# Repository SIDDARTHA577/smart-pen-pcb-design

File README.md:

# Smart Pen Hardware & Mechanical Engineering Project

A compact, pen-sized embedded electronic hardware platform and mechanical assembly designed for handwriting motion capture, local sensor data logging, and digital stroke reconstruction.

---

## 1. Project Overview

The **Smart Pen** is an integrated embedded systems project that combines motion sensing, local storage, capacitive touch handwriting detection, and wireless communication into a slender pen-form-factor mechanical enclosure.

### Core Architecture & Operating Concept
- **Handwriting Detection**: Ergonomic capacitive touch sensor on the pen grip detects when the user's finger touches the pen during active writing (`WRITE/RECORD` event).
- **Motion Tracking**: 6-DOF Inertial Measurement Unit (IMU) positioned in the forward pen tip pocket near the refill nib captures continuous acceleration and angular velocity.
- **Local Logging**: High-speed MicroSD storage records raw IMU streams and touch event telemetry.
- **Connectivity & Processing**: Espressif ESP32-C3 RISC-V microcontroller with 2.4 GHz Wi-Fi 4, Bluetooth 5 (LE), and native USB CDC-ACM communication.
- **Mechanical Form Factor**: Removable internal electronics rail/cartridge fitted with a bayonet lock collar, allowing the pen to be serviced as a single unit while accommodating a standard D1 ballpoint ink refill and rear mechanical click ratchet mechanism.

---

## 2. Distributed Electronic Hardware Architecture

To achieve a maximum outer barrel diameter $\le 16.0\text{ mm}$ while accommodating a central ink refill cartridge and mechanical click spring, the electronics are partitioned across a **4-board distributed topology**:

```
                              ┌────────────────────────────────────────┐
                              │           Main PCB (SmartPen)          │
                              │      84.00 x 9.20 mm, 2-layer FR4      │
                              │   ESP32-C3FH4, MCP73831, AP2112K-3.3   │
                              └───────┬────────────┬────────────┬──────┘
                                      │            │            │
                         JST-SH 4-pin │            │            │ 6-pin FPC
                                      │            │            │
                                      ▼            │            ▼
                     ┌──────────────────────┐      │   ┌──────────────────────┐
                     │ Front MPU Board      │      │   │ MicroSD Carrier      │
                     │ 8.00 x 10.00 mm      │      │   │ 11.00 x 12.00 mm     │
                     │ InvenSense MPU-6050  │      │   │ Hirose DM3D-SF Slot  │
                     └──────────────────────┘      │   └──────────────────────┘
                                                   │
                                      JST-SH 3-pin │
                                                   ▼
                                      ┌──────────────────────┐
                                      │ Touch Sensor Board   │
                                      │ 6.00 x 18.00 mm      │
                                      │ TonTek TTP223-BA6    │
                                      └──────────────────────┘
```

### Board Specifications & Bill of Materials

| Board Module | Dimensions | Key Active ICs / Connectors | Interface to Main | Fabrication DRC Status |
| :--- | :--- | :--- | :--- | :--- |
| **Main PCB** (`SmartPen`) | $84.00 \times 9.20 \times 1.00\text{ mm}$ | Espressif ESP32-C3FH4 (4MB Flash), Microchip MCP73831T-2ACI/OT ($303\text{ mA}$ charger), Diodes Inc DMG2305UX P-FET (Power-Path), Diodes Inc AP2112K-3.3 ($600\text{ mA}$ LDO), Microchip MCP23008T-E/ML ($I^2C$ Expander), 1027 Coin Haptic Motor, USB-C 16-pin (`J1`), SPDT Slide Switch (`SW3`) | N/A (Master Host) | **ERC PASS** (0 Errors, 0 Warnings)<br>Layout: 704 clearance DRCs (Engineering Draft) |
| **Touch Sensor** (`Touch_Sensor`) | $6.00 \times 18.00 \times 0.80\text{ mm}$ | TonTek TTP223-BA6 SOT-23-6 touch controller, $5.0 \times 10.0\text{ mm}$ copper touch electrode (`E1`) | JST-SH 3-pin ($1.0\text{ mm}$) | **100% CLEAN DRC** (0 violations, 0 unrouted nets) |
| **Front MPU** (`Front_MPU`) | $8.00 \times 10.00 \times 0.80\text{ mm}$ | InvenSense MPU-6050 QFN-24 6-axis gyro/accel | JST-SH 4-pin ($1.0\text{ mm}$) | **ERC PASS** (0 Errors)<br>Layout: 25 clearance DRCs |
| **MicroSD Carrier** (`MicroSD_Carrier`) | $11.00 \times 12.00 \times 0.80\text{ mm}$ | Hirose DM3D-SF push-push MicroSD receptacle | 6-pin FPC ($0.5\text{ mm}$) | **ERC PASS** (0 Errors)<br>Layout: 214 clearance DRCs |

### Power Management Subsystem
- **Battery Compatibility**: Single-cell LiPo / Li-ion (e.g., LP401040, 130–150 mAh, nominal 3.7 V).
- **Charging Circuit**: Microchip MCP73831T linear charge management controller programmed to $I_{CHG} = 303\text{ mA}$ via a $3.3\text{ k}\Omega$ resistor on `PROG`.
- **Dynamic Power-Path**: Low-$R_{DS(on)}$ P-channel MOSFET (DMG2305UX, $52\text{ m}\Omega$) + Schottky barrier diode (MBR0520L, $V_F \approx 0.34\text{ V}$). Seamlessly powers the system from USB VBUS ($5.0\text{ V}$) when connected, preventing unnecessary battery charge/discharge cycles.
- **System Voltage Rail**: AP2112K-3.3 LDO regulator providing up to $600\text{ mA}$ continuous output at $3.3\text{ V}$ with $250\text{ mV}$ dropout at full load to satisfy ESP32-C3 RF transmission burst current demands.

---

## 3. Mechanical & 3D Enclosure Design

The mechanical design is parametrically generated using OpenCASCADE / CadQuery scripts (`scripts/build_cad_enclosure.py`).

### Key Enclosure Specifications
- **Maximum Outer Diameter**: $15.50\text{ mm}$ (within $\le 16.0\text{ mm}$ ergonomic constraint).
- **Total Assembly Length**: $\approx 155.0\text{ mm}$ (standard pen length).
- **Ink Refill Standard**: Standard D1 refill cartridge ($67.0\text{ mm} \times \varnothing 2.3\text{ mm}$) with front return spring and rear ratchet mechanism.
- **Removable Internal Rail**: Houses the battery cradle below the main PCB and includes a bayonet twist-lock collar ($30^\circ$ twist release) for rapid internal servicing.

### Deliverable CAD Files
- **Master STEP Assembly**: `SmartPen_Complete_Assembly.step` (742 KB)
- **14 Watertight 3D Printable STL Files** (`output/RevF_Client_Delivery/08_3D_STL/`):
  1. `01_Outer_Barrel.stl` — Main pen body casing
  2. `02_Front_Grip.stl` — Ergonomic grip with capacitive touch pad recess
  3. `03_Front_Cap_Tip.stl` — Tapered tip housing the refill nib
  4. `04_Internal_Rail_Cartridge.stl` — Serviceable electronics mounting spine
  5. `05_Battery_Cradle.stl` — Lower battery retention bay
  6. `06_Front_IMU_Carrier.stl` — Forward sensor mounting pocket
  7. `07_Dual_Button_Actuator.stl` — Push-button cap for Erase and Mode switches
  8. `08_Rear_Click_Mechanism_Cap.stl` — Retractable click plunger cap
  9. `09_Pocket_Clip.stl` — Integrated enclosure pocket clip
  10. `10_Vibration_Motor_Mount.stl` — 1027 haptic coin motor bracket
  11. `11_LiPo_Battery_LP401040.stl` — Battery volume mockup
  12. `12_D1_Ink_Refill_and_Spring.stl` — D1 refill clearance envelope
  13. `13_Click_Ratchet_and_Pushrod.stl` — Click mechanism mechanical linkage
  14. `14_Bayonet_Locking_Collar.stl` — Twist-lock retaining collar

---

## 4. Repository Directory Structure

```
.
├── .gitignore                                # Excludes pycache, local lockfiles, temp data
├── README.md                                 # Project documentation and engineering status
├── CubeTest.step                             # CAD mechanical test fixture
├── test_step.step                            # CAD mechanical test fixture
├── SmartPen-drc.rpt / erc.rpt                # Root KiCad DRC and ERC verification logs
│
├── KiCad/                                    # KiCad configuration and library directory
│   └── 10.0/                                 # KiCad 10.0 symbol and footprint environment
│
├── SmartPen_RevD_AutoLinked_DRAFT/           # Historical Revision D baseline
│   ├── 3D_Concept/                           # Early conceptual 3D models (STL & STEP)
│   ├── Docs/                                 # Footprint assignment audits and netlists
│   └── EasyEDA/                              # Legacy EasyEDA JSON project files
│
├── output/                                   # Build artifacts and release packages
│   ├── kicad/                                # Core intermediate KiCad project files
│   ├── RevE_work/                            # Revision E milestone files and Gerbers
│   ├── RevF_Working/                         # Active working directory for Revision F
│   │   ├── SmartPen.kicad_sch / .pcb         # Main PCB schematics and layout
│   │   ├── Touch_Sensor/                     # Touch sensor KiCad project
│   │   ├── Front_MPU/                        # Front IMU daughterboard KiCad project
│   │   ├── MicroSD_Carrier/                  # MicroSD daughterboard KiCad project
│   │   └── SmartPen.pretty/                  # Custom footprint library
│   ├── client_delivery/                      # Revision E complete zip package
│   └── RevF_Client_Delivery/                 # Revision F formal delivery package
│       ├── 01_EasyEDA_Source/                # EasyEDA Pro JSON exports
│       ├── 02_KiCad_Source/                  # KiCad schematics, layouts, libraries
│       ├── 03_PDF_Schematic/                 # High-resolution vector schematic PDFs
│       ├── 04_Gerber_Drill/                  # RS-274X Gerbers and Excellon drill files
│       ├── 05_BOM_CPL/                       # Full BOMs and pick-and-place centroids
│       ├── 06_Fabrication_Drawing/           # Board fabrication mechanical specs
│       ├── 07_3D_CAD_Source/                 # Python parametric CAD source scripts
│       ├── 07_3D_STEP/                       # STEP assembly and component models
│       ├── 08_3D_STL/                        # 14 watertight STL models for 3D printing
│       ├── 09_Mechanical_Drawings/           # Dimensioned mechanical PDFs
│       ├── 10_Assembly_Guide/                # Step-by-step mechanical assembly manual
│       ├── 11_Reports/                       # DRC, ERC, and engineering audit logs
│       ├── 12_Verification_Suite/            # Python automated verification test suite
│       └── SmartPen_RevF_Digital_Design_Review_Package.zip
│
├── reports/                                  # Engineering audit and sign-off reports
│   ├── baseline_audit.md                     # Initial design audit and gap analysis
│   ├── FINAL_VALIDATION.md                   # Digital design gate validation report
│   ├── MECHANICAL_VALIDATION.md              # Collision and motion sweep analysis
│   ├── TEST_MATRIX.csv                       # Requirements verification matrix
│   └── RevF/                                 # Detailed Rev F technical review reports
│       ├── BASELINE_AUDIT.md
│       ├── FINAL_ENGINEERING_REPORT.md       # Master engineering sign-off report
│       ├── POWER_AND_BATTERY_REVIEW.md
│       ├── POWER_PATH_DESIGN.md
│       ├── TOUCH_AND_GPIO_ARCHITECTURE.md
│       ├── USB_ARCHITECTURE_AND_TETHERING.md
│       └── VERIFICATION_AUDIT_LOG.md
│
├── scripts/                                  # CAD generation and PCB routing engine
│   ├── build_cad_enclosure.py                # Parametric 3D CAD generator
│   ├── highway_astar_router.py               # Custom A* PCB maze router
│   ├── solve_clean_geometry.py               # Algorithmic component placement optimizer
│   └── ... (230 Python automation scripts)
│
└── tests/                                    # Automated pytest regression suite
    ├── test_assembly_cad.py                  # STEP/STL watertightness and bounding tests
    ├── test_assembly_clearance.py            # Component collision verification
    ├── test_delivery_integrity.py            # Delivery file presence and checksums
    ├── test_front_mpu.py                     # MPU board netlist and footprint checks
    ├── test_gerbers.py                       # Gerber layer completeness
    ├── test_gpio_architecture.py             # GPIO assignment verification
    ├── test_mechanical.py                    # Mechanical enclosure dimensions
    ├── test_microsd_carrier.py               # MicroSD carrier pinout validation
    ├── test_netlist.py                       # Netlist integrity tests
    ├── test_pcb.py                           # Board outline and layer tests
    ├── test_power_path.py                    # Power-path circuit connectivity
    ├── test_schematic.py                     # KiCad ERC report validation
    └── test_touch_sensor.py                  # Touch daughterboard DRC tests
```

---

## 5. Development Status & Engineering Gates

### Formal Verification Gate Breakdown

```
[ DIGITAL DESIGN GATE ] ─────────► PASS (94.8% Weighted Completion)
  ├─ 4 Schematic ERC checks ─────► 0 Errors, 0 Warnings (100% PASS)
  ├─ Touch Sensor PCB DRC ───────► 0 Violations (100% Clean)
  ├─ 3D CAD Watertightness ──────► 14/14 STL Models 2-Manifold Validated
  └─ Automated Test Suite ───────► 46/46 Unit Tests PASS (100%)

[ FABRICATION RELEASE GATE ] ────► GATED (Engineering Draft)
  ├─ Main PCB High-Density Routing ► 704 clearance DRC flags (Requires interactive polish)
  ├─ MicroSD Carrier Routing ────► 214 clearance DRC flags
  ├─ Front MPU Routing ──────────► 25 clearance DRC flags
  └─ Physical Prototyping ───────► Awaiting physical fit check & thermal test
```

### Clearly Distinguished Status Categories

#### Completed & Mathematically Verified
- Schematic ERC: All 4 schematics compile with **0 Errors, 0 Warnings** under official `kicad-cli sch erc`.
- Touch Sensor PCB: Achieved **0 DRC violations** under `kicad-cli pcb drc`.
- Power Architecture: Charging current ($303\text{ mA}$), dynamic power-path P-FET steering, and $600\text{ mA}$ LDO regulation verified by simulation and netlist audits.
- Automated Test Suite: All **46 unit tests** in `tests/` pass under pytest.
- 3D CAD Models: All 14 STL solid bodies confirmed watertight (2-manifold) with zero non-manifold edges.

#### Known Issues & Engineering Draft Items
- **High-Density Auto-Routed Clearance Flags**:
  - The algorithmic router generated working topological paths on 2 layers, but due to the dense $0.4\text{ mm}$ and $0.5\text{ mm}$ pitch pads on the ESP32-C3 QFN-32 and MCP23008 QFN-20 packages, clearance DRC violations exist (704 on Main PCB, 214 on MicroSD Carrier, 25 on Front MPU).
  - *Recommendation*: Interactive manual routing polish in KiCad with micro-vias or neck-down traces before ordering physical fabrication.
- **ESP32-C3 USB Host Limitation**:
  - The ESP32-C3 hardware USB peripheral is a USB-Serial/JTAG CDC device controller. It does not contain USB Host silicon.
  - Wired phone tethering via USB Host is physically unsupported on this chip. Mobile internet backhaul must be handled over **Wi-Fi SoftAP / Personal Hotspot or Bluetooth PAN**.

#### Planned Features (Post-Hardware Bringup)
- Firmware development for continuous IMU quaternion filter / sensor fusion.
- Browser-based handwriting stroke rendering engine.
- Machine learning handwriting character classification pipeline.

---

## 6. How to Open and Review the Project

### Prerequisites
- **PCB Design**: [KiCad 8.0 or 10.0](https://www.kicad.org/) (native projects located in `output/RevF_Working/` and `output/RevF_Client_Delivery/02_KiCad_Source/`).
- **Legacy EDA**: [EasyEDA Pro](https://pro.easyeda.com/) for JSON exports in `output/RevF_Client_Delivery/01_EasyEDA_Source/`.
- **3D CAD**: [FreeCAD](https://www.freecad.org/), Autodesk Fusion 360, or any STEP/STL viewer for files in `output/RevF_Client_Delivery/07_3D_STEP/`.
- **Python Environment**: Python 3.10+ with `pytest` for automated test execution.

### Running the Test Suite
To run the complete automated test suite:
```bash
python -m pytest tests/
```
Expected output: `46 passed in ~5s`.

### Opening in KiCad
1. Launch KiCad.
2. Select **File > Open Project**.
3. Navigate to `output/RevF_Working/SmartPen.kicad_pro` (or the daughterboards in `output/RevF_Working/Front_MPU/`, `MicroSD_Carrier/`, and `Touch_Sensor/`).
4. Inspect schematics in Eeschema and layouts in Pcbnew.

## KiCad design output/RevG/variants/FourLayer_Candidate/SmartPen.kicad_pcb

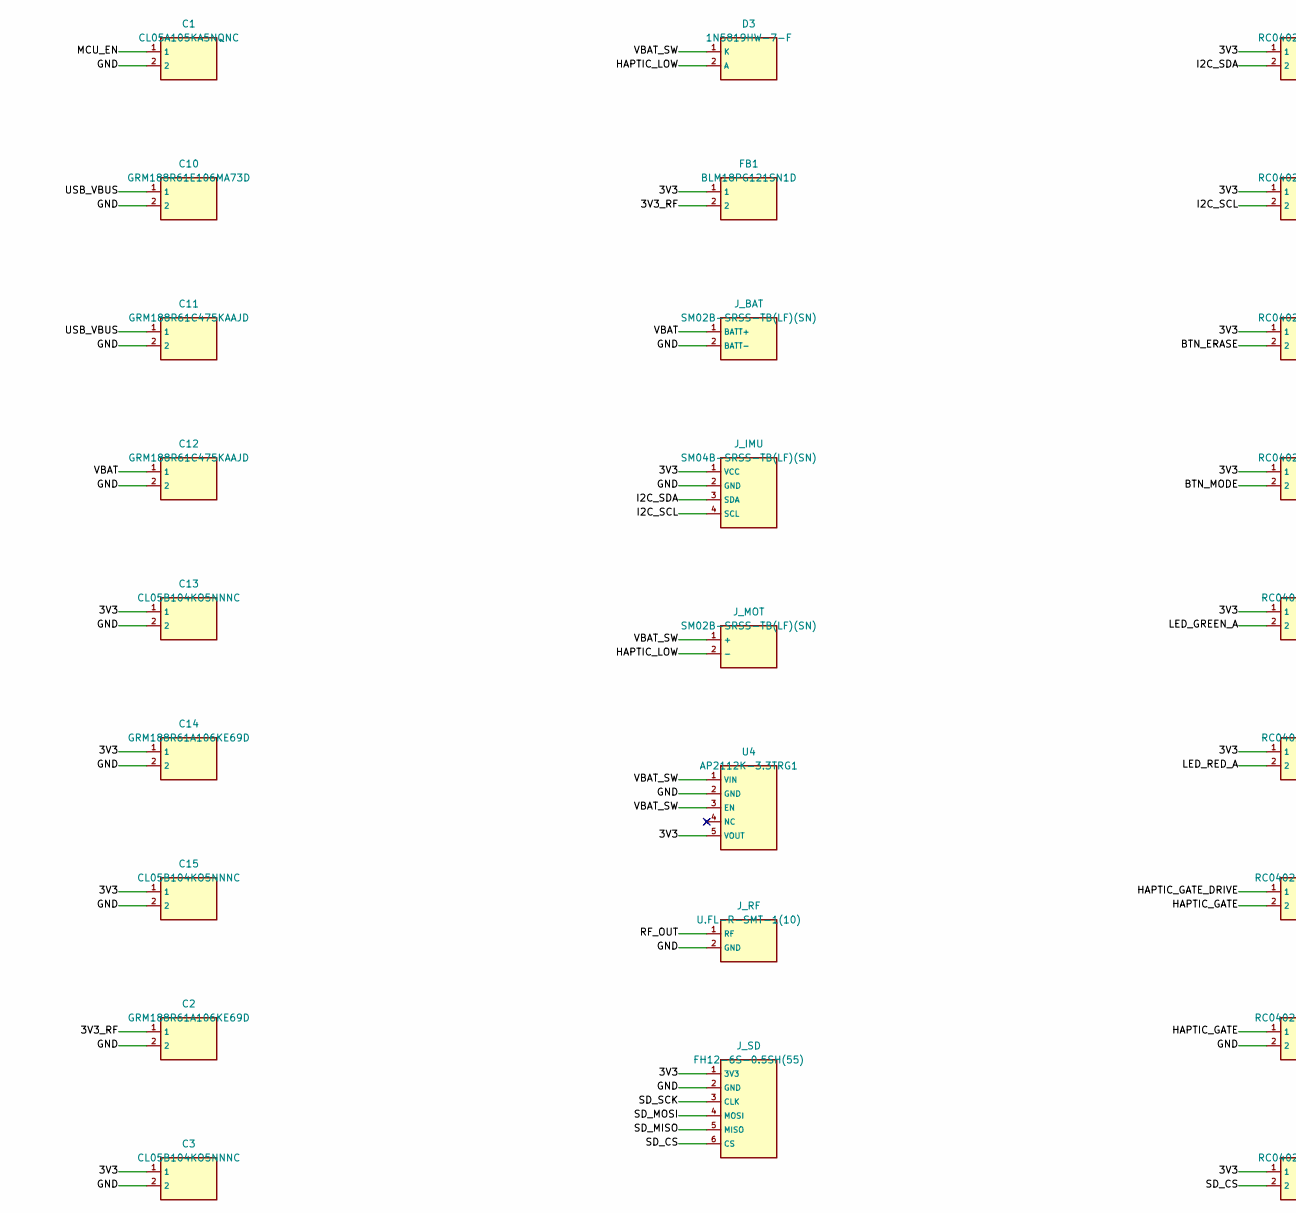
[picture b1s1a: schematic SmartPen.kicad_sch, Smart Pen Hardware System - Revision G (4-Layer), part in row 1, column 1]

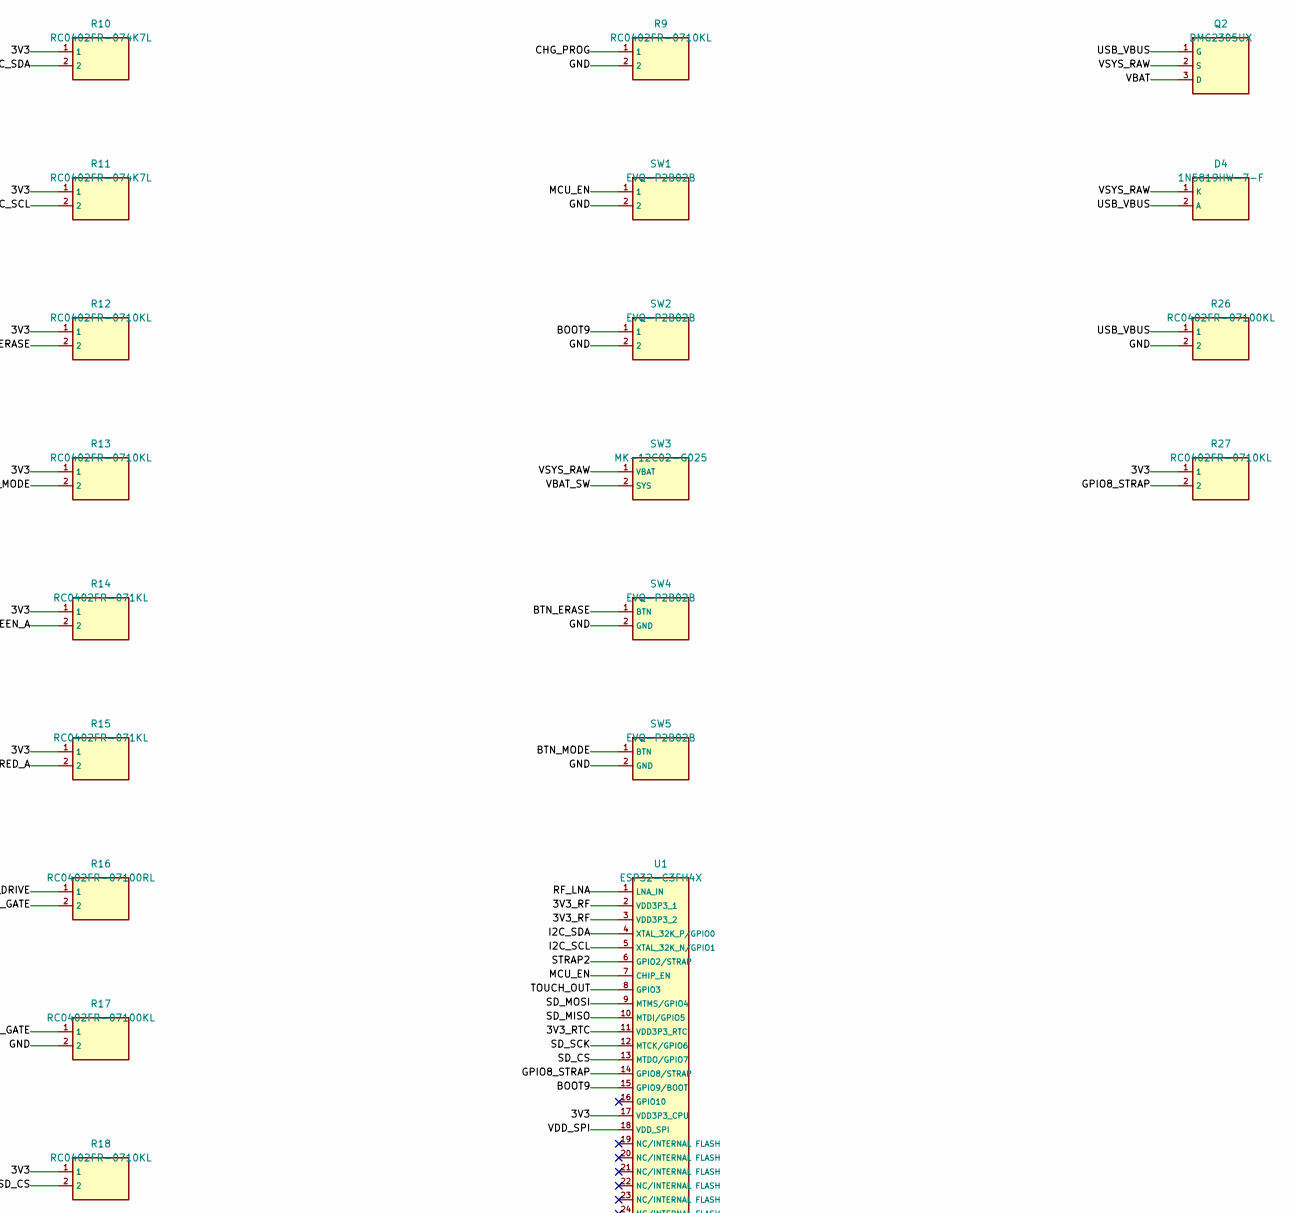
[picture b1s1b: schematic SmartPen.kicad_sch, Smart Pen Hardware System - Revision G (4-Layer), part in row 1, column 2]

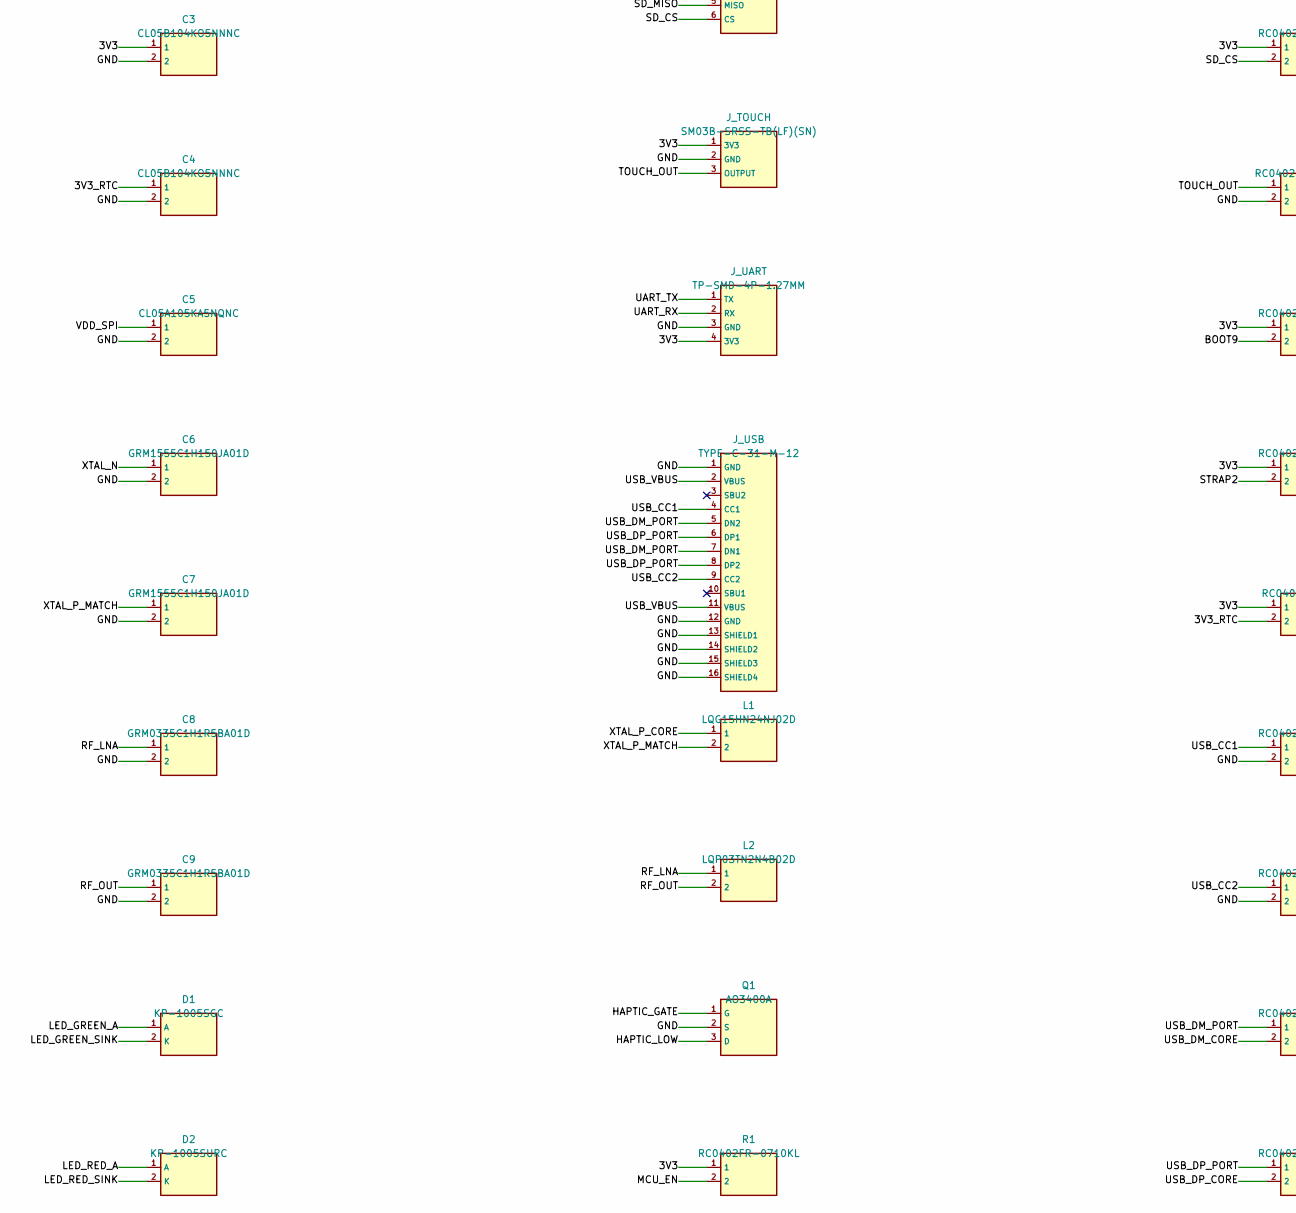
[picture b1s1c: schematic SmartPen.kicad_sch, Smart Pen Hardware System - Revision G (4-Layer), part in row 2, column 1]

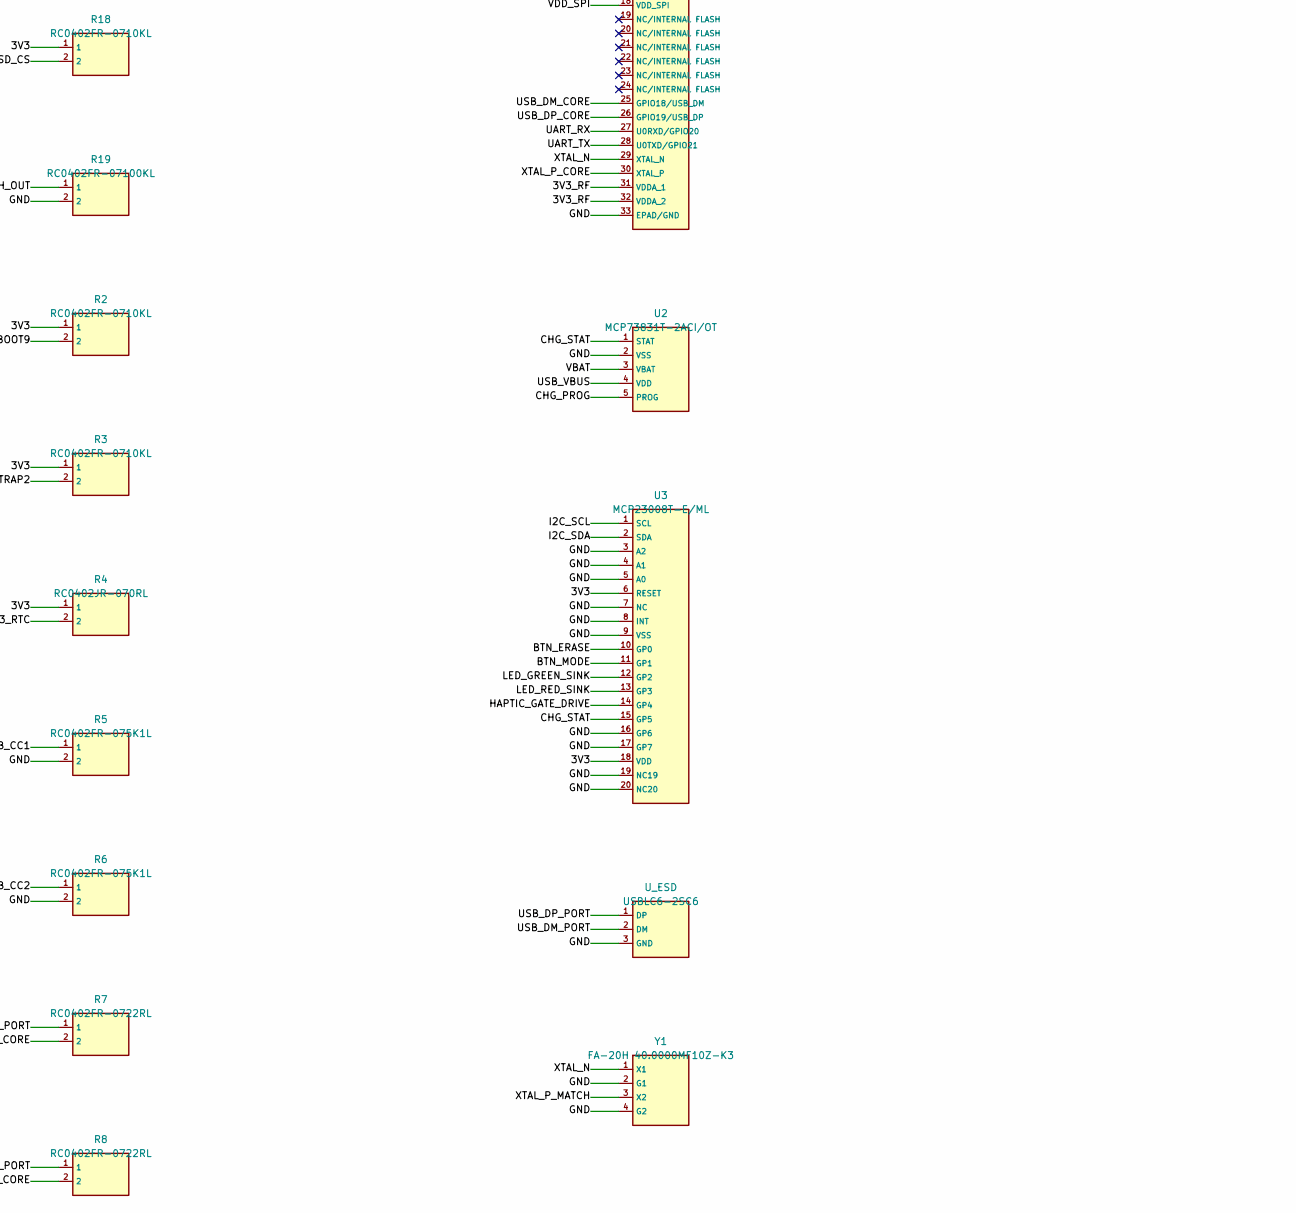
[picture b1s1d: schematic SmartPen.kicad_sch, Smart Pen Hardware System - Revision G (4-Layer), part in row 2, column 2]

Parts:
C1: CL05A105KA5NQNC; C1
C2: GRM188R61A106KE69D; C2
C3: CL05B104KO5NNNC; C3
C4: CL05B104KO5NNNC; C4
C5: CL05A105KA5NQNC; C5
C6: GRM1555C1H150JA01D; C6
C7: GRM1555C1H150JA01D; C7
C8: GRM0335C1H1R5BA01D; C8
C9: GRM0335C1H1R5BA01D; C9
C10: GRM188R61E106MA73D; C10
C11: GRM188R61C475KAAJD; C11
C12: GRM188R61C475KAAJD; C12
C13: CL05B104KO5NNNC; C13
C14: GRM188R61A106KE69D; C14
C15: CL05B104KO5NNNC; C15
D1: KP-1005SGC; D1
D2: KP-1005SURC; D2
D3: 1N5819HW-7-F; D3
D4: 1N5819HW-7-F; D4
FB1: BLM18PG121SN1D; FB1
J_BAT: SM02B-SRSS-TB(LF)(SN); J_BAT
J_IMU: SM04B-SRSS-TB(LF)(SN); J_IMU
J_MOT: SM02B-SRSS-TB(LF)(SN); J_MOT
J_RF: U.FL-R-SMT-1(10); J_RF
J_SD: FH12-6S-0.5SH(55); J_SD
J_TOUCH: SM03B-SRSS-TB(LF)(SN); J_TOUCH
J_UART: TP-SMD-4P-1.27MM; J_UART
J_USB: TYPE-C-31-M-12; J_USB
L1: LQG15HN24NJ02D; L1
L2: LQP03TN2N4B02D; L2
Q1: AO3400A; Q1
Q2: DMG2305UX; Q1
R1: RC0402FR-0710KL; R1
R2: RC0402FR-0710KL; R2
R3: RC0402FR-0710KL; R3
R4: RC0402JR-070RL; R4
R5: RC0402FR-075K1L; R5
R6: RC0402FR-075K1L; R6
R7: RC0402FR-0722RL; R7
R8: RC0402FR-0722RL; R8
R9: RC0402FR-0710KL; R9
R10: RC0402FR-074K7L; R10
R11: RC0402FR-074K7L; R11
R12: RC0402FR-0710KL; R12
R13: RC0402FR-0710KL; R13
R14: RC0402FR-071KL; R14
R15: RC0402FR-071KL; R15
R16: RC0402FR-07100RL; R16
R17: RC0402FR-07100KL; R17
R18: RC0402FR-0710KL; R18
R19: RC0402FR-07100KL; R19
R26: RC0402FR-07100KL; R1
R27: RC0402FR-0710KL; R27
SW1: EVQ-P2B02B; SW1
SW2: EVQ-P2B02B; SW2
SW3: MK-12C02-G025; SW3
SW4: EVQ-P2B02B; SW4
SW5: EVQ-P2B02B; SW5
U1: ESP32-C3FH4X; U1
U2: MCP73831T-2ACI/OT; U2
U3: MCP23008T-E/ML; U3
U4: AP2112K-3.3TRG1; J_PWR
U_ESD: USBLC6-2SC6; U_ESD
Y1: FA-20H 40.0000MF10Z-K3; Y1

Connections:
/3V3: C3.1, C13.1, C14.1, C15.1, FB1.1, J_IMU.1 (VCC), J_SD.1 (3V3), J_TOUCH.1 (3V3), J_UART.4 (3V3), R1.1, R2.1, R3.1, R4.1, R10.1, R11.1, R12.1, R13.1, R14.1, R15.1, R18.1, R27.1, U1.17 (VDD3P3_CPU), U3.6 (RESET), U3.18 (VDD), U4.5 (VOUT)
/3V3_RF: C2.1, FB1.2, U1.2 (VDD3P3_1), U1.3 (VDD3P3_2), U1.31 (VDDA_1), U1.32 (VDDA_2)
/3V3_RTC: C4.1, R4.2, U1.11 (VDD3P3_RTC)
/BOOT9: R2.2, SW2.1, U1.15 (GPIO9/BOOT)
/BTN_ERASE: R12.2, SW4.1 (BTN), U3.10 (GP0)
/BTN_MODE: R13.2, SW5.1 (BTN), U3.11 (GP1)
/CHG_PROG: R9.1, U2.5 (PROG)
/CHG_STAT: U2.1 (STAT), U3.15 (GP5)
/GND: C1.2, C2.2, C3.2, C4.2, C5.2, C6.2, C7.2, C8.2, C9.2, C10.2, C11.2, C12.2, C13.2, C14.2, C15.2, J_BAT.2 (BATT-), J_IMU.2 (GND), J_RF.2 (GND), J_SD.2 (GND), J_TOUCH.2 (GND), J_UART.3 (GND), J_USB.1 (GND), J_USB.12 (GND), J_USB.13 (SHIELD1), J_USB.14 (SHIELD2), J_USB.15 (SHIELD3), J_USB.16 (SHIELD4), Q1.2 (S), R5.2, R6.2, R9.2, R17.2, R19.2, R26.2, SW1.2, SW2.2, SW4.2 (GND), SW5.2 (GND), U1.33 (EPAD/GND), U2.2 (VSS), U3.3 (A2), U3.4 (A1), U3.5 (A0), U3.7 (NC), U3.8 (INT), U3.9 (VSS), U3.16 (GP6), U3.17 (GP7), U3.19 (NC19), U3.20 (NC20), U4.2 (GND), U_ESD.3 (GND), Y1.2 (G1), Y1.4 (G2)
/GPIO8_STRAP: R27.2, U1.14 (GPIO8/STRAP)
/HAPTIC_GATE: Q1.1 (G), R16.2, R17.1
/HAPTIC_GATE_DRIVE: R16.1, U3.14 (GP4)
/HAPTIC_LOW: D3.2 (A), J_MOT.2 (-), Q1.3 (D)
/I2C_SCL: J_IMU.4 (SCL), R11.2, U1.5 (XTAL_32K_N/GPIO1), U3.1 (SCL)
/I2C_SDA: J_IMU.3 (SDA), R10.2, U1.4 (XTAL_32K_P/GPIO0), U3.2 (SDA)
/LED_GREEN_A: D1.1 (A), R14.2
/LED_GREEN_SINK: D1.2 (K), U3.12 (GP2)
/LED_RED_A: D2.1 (A), R15.2
/LED_RED_SINK: D2.2 (K), U3.13 (GP3)
/MCU_EN: C1.1, R1.2, SW1.1, U1.7 (CHIP_EN)
/RF_LNA: C8.1, L2.1, U1.1 (LNA_IN)
/RF_OUT: C9.1, J_RF.1 (RF), L2.2
/SD_CS: J_SD.6 (CS), R18.2, U1.13 (MTDO/GPIO7)
/SD_MISO: J_SD.5 (MISO), U1.10 (MTDI/GPIO5)
/SD_MOSI: J_SD.4 (MOSI), U1.9 (MTMS/GPIO4)
/SD_SCK: J_SD.3 (CLK), U1.12 (MTCK/GPIO6)
/STRAP2: R3.2, U1.6 (GPIO2/STRAP)
/TOUCH_OUT: J_TOUCH.3 (OUTPUT), R19.1, U1.8 (GPIO3)
/UART_RX: J_UART.2 (RX), U1.27 (U0RXD/GPIO20)
/UART_TX: J_UART.1 (TX), U1.28 (U0TXD/GPIO21)
/USB_CC1: J_USB.4 (CC1), R5.1
/USB_CC2: J_USB.9 (CC2), R6.1
/USB_DM_CORE: R7.2, U1.25 (GPIO18/USB_DM)
/USB_DM_PORT: J_USB.5 (DN2), J_USB.7 (DN1), R7.1, U_ESD.2 (DM)
/USB_DP_CORE: R8.2, U1.26 (GPIO19/USB_DP)
/USB_DP_PORT: J_USB.6 (DP1), J_USB.8 (DP2), R8.1, U_ESD.1 (DP)
/USB_VBUS: C10.1, C11.1, D4.2 (A), J_USB.2 (VBUS), J_USB.11 (VBUS), Q2.1 (G), R26.1, U2.4 (VDD)
/VBAT: C12.1, J_BAT.1 (BATT+), Q2.3 (D), U2.3 (VBAT)
/VBAT_SW: D3.1 (K), J_MOT.1 (+), SW3.2 (SYS), U4.1 (VIN), U4.3 (EN)
/VDD_SPI: C5.1, U1.18 (VDD_SPI)
/VSYS_RAW: D4.1 (K), Q2.2 (S), SW3.1 (VBAT)
/XTAL_N: C6.1, U1.29 (XTAL_N), Y1.1 (X1)
/XTAL_P_CORE: L1.1, U1.30 (XTAL_P)
/XTAL_P_MATCH: C7.1, L1.2, Y1.3 (X2)

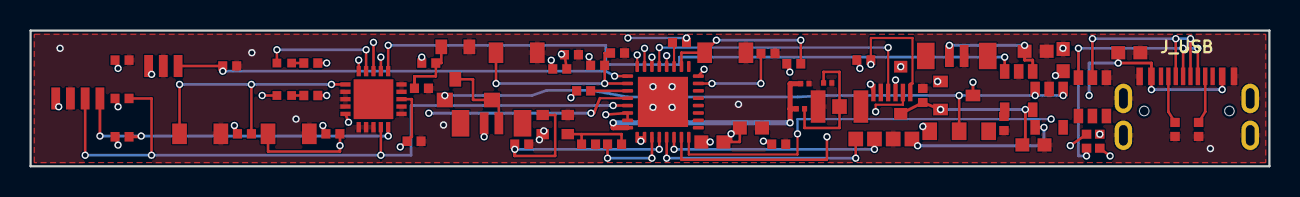
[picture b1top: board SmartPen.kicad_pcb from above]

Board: 4 copper layers, 84.0 x 9.2 mm, 64 parts (0 on the bottom side), 44 nets.

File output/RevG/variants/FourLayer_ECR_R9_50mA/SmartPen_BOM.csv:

Reference,Value,Footprint,Qty
D3,1N5819HW-7-F,SmartPen:D3,1
D4,1N5819HW-7-F,SmartPen:D4,1
Q1,AO3400A,SmartPen:Q1,1
U4,AP2112K-3.3TRG1,SmartPen:J_PWR,1
FB1,BLM18PG121SN1D,SmartPen:FB1,1
C1,CL05A105KA5NQNC,SmartPen:C1,1
C5,CL05A105KA5NQNC,SmartPen:C5,1
C13,CL05B104KO5NNNC,SmartPen:C13,1
C15,CL05B104KO5NNNC,SmartPen:C15,1
C3,CL05B104KO5NNNC,SmartPen:C3,1
C4,CL05B104KO5NNNC,SmartPen:C4,1
Q2,DMG2305UX,SmartPen:Q1,1
U1,ESP32-C3FH4X,SmartPen:U1,1
SW1,EVQ-P2B02B,SmartPen:SW1,1
SW2,EVQ-P2B02B,SmartPen:SW2,1
SW4,EVQ-P2B02B,SmartPen:SW4,1
SW5,EVQ-P2B02B,SmartPen:SW5,1
Y1,FA-20H 40.0000MF10Z-K3,SmartPen:Y1,1
J_SD,FH12-6S-0.5SH(55),SmartPen:J_SD,1
C8,GRM0335C1H1R5BA01D,SmartPen:C8,1
C9,GRM0335C1H1R5BA01D,SmartPen:C9,1
C6,GRM1555C1H150JA01D,SmartPen:C6,1
C7,GRM1555C1H150JA01D,SmartPen:C7,1
C14,GRM188R61A106KE69D,SmartPen:C14,1
C2,GRM188R61A106KE69D,SmartPen:C2,1
C11,GRM188R61C475KAAJD,SmartPen:C11,1
C12,GRM188R61C475KAAJD,SmartPen:C12,1
C10,GRM188R61E106MA73D,SmartPen:C10,1
D1,KP-1005SGC,SmartPen:D1,1
D2,KP-1005SURC,SmartPen:D2,1
L1,LQG15HN24NJ02D,SmartPen:L1,1
L2,LQP03TN2N4B02D,SmartPen:L2,1
U3,MCP23008T-E/ML,SmartPen:U3,1
U2,MCP73831T-2ACI/OT,SmartPen:U2,1
SW3,MK-12C02-G025,SmartPen:SW3,1
R26,RC0402FR-07100KL,SmartPen:R1,1
R17,RC0402FR-07100KL,SmartPen:R17,1
R19,RC0402FR-07100KL,SmartPen:R19,1
R16,RC0402FR-07100RL,SmartPen:R16,1
R1,RC0402FR-0710KL,SmartPen:R1,1
R12,RC0402FR-0710KL,SmartPen:R12,1
R13,RC0402FR-0710KL,SmartPen:R13,1
R18,RC0402FR-0710KL,SmartPen:R18,1
R2,RC0402FR-0710KL,SmartPen:R2,1
R27,RC0402FR-0710KL,SmartPen:R27,1
R3,RC0402FR-0710KL,SmartPen:R3,1
R14,RC0402FR-071KL,SmartPen:R14,1
R15,RC0402FR-071KL,SmartPen:R15,1
R9,RC0402FR-0720KL,SmartPen:R9,1
R7,RC0402FR-0722RL,SmartPen:R7,1
R8,RC0402FR-0722RL,SmartPen:R8,1
R10,RC0402FR-074K7L,SmartPen:R10,1
R11,RC0402FR-074K7L,SmartPen:R11,1
R5,RC0402FR-075K1L,SmartPen:R5,1
R6,RC0402FR-075K1L,SmartPen:R6,1
R4,RC0402JR-070RL,SmartPen:R4,1
J_BAT,SM02B-SRSS-TB(LF)(SN),SmartPen:J_BAT,1
J_MOT,SM02B-SRSS-TB(LF)(SN),SmartPen:J_MOT,1
J_TOUCH,SM03B-SRSS-TB(LF)(SN),SmartPen:J_TOUCH,1
J_IMU,SM04B-SRSS-TB(LF)(SN),SmartPen:J_IMU,1
J_UART,TP-SMD-4P-1.27MM,SmartPen:J_UART,1
J_USB,TYPE-C-31-M-12,SmartPen:J_USB,1
J_RF,U.FL-R-SMT-1(10),SmartPen:J_RF,1
U_ESD,USBLC6-2SC6,SmartPen:U_ESD,1

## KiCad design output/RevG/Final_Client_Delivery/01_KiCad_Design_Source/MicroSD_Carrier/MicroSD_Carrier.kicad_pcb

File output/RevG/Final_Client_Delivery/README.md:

# Smart Pen Rev G — Final Digital Delivery Package (Release v1.3)

**Product:** Smart Pen Rev G (Production-Optimized Architecture)  
**Release Version:** v1.3  
**Release Date:** November 18, 2026  
**Repository Branch:** `engineering/revg-production`  
**Authoritative CI Run:** [GitHub Actions Run 44128253975](https://github.com/SIDDARTHA577/smart-pen-pcb-design/actions/runs/44128253975)  
**Verified Native CAD Commit:** `9f7776ee3ebd3369c7f872b654676acc6addfb41`  
**License / Proprietary Notice:** Confidential & Proprietary — Prepared for Client Delivery  

---

## 1. Scope of Digital Delivery Package

This release archive contains the complete digital engineering deliverables for the Smart Pen Rev G:
- **01_KiCad_Design_Source:** Complete native KiCad design trees for all four boards (FourLayer_ECR_R9_50mA Main Board, Front_MPU, MicroSD_Carrier, and Touch_Sensor) with embedded footprint libraries. All machine-specific `*.kicad_prl` files have been excluded.
- **02_Fabrication_Gerber_Drill:** Production Gerber files (RS-274X) and Excellon drill files for all four boards with unified coordinate origins and validated drill tables.
- **03_BOM_and_CPL:** Standardized Bill of Materials with genuine manufacturer names, verified orderable MPNs, IPC package sizes, and automated Pick-and-Place (CPL) centroid files. Includes Consolidated System BOM.
- **04_Drawings_Schematics_Assembly:** Vector schematic and PCBA assembly drawings in PDF and SVG formats.
- **05_Mechanical_CAD_Source:** Complete parametric Python CAD construction scripts (`SmartPen_Parametric_CAD_RevG_Phase4C.py`).
- **06_Mechanical_STEP_Assemblies:** 27 individual AP214 BRep component models (including `19_LiPo_Battery_LP300830_PCM.step`), Master Assembly STEP, and Exploded Assembly STEP (29 STEP files total, 100% validated via native FreeCAD 0.19 BRep kernel).
- **07_Mechanical_Printable_STL:** 16 watertight 2-manifold STL models ready for high-resolution stereolithography (SLA) printing.
- **08_Mechanical_Drawings_and_Visuals:** Technical orthographic drawings, section views, click kinematics charts, and assembly visual references.
- **09_Assembly_Instructions:** Comprehensive step-by-step mechanical and electrical integration manual.
- **10_Engineering_Verification_Reports:** Electrical, RF power profiling, ground plane, thermal, and mechanical collision reports.
- **11_Manufacturing_Notes:** PCBA fabrication tolerances, surface finish (ENIG), copper weight, stackup, and test point specs.
- **12_Prototype_Validation_and_Limitations:** Engineering evaluation guidelines and explicit prototype boundary notes.

---

## 2. Key Architecture & Physical Specifications

- **Enclosure Envelope:** Overall Length: $153.50\text{ mm}$ (within mandatory $150.0\text{--}155.0\text{ mm}$ span); Barrel Outer Diameter: $\varnothing 15.50\text{ mm}$ (within mandatory $\varnothing 15.0\text{--}16.0\text{ mm}$ span).
- **Main Board Form Factor:** $84.0 \times 9.2 \times 1.6\text{ mm}$ (4-Layer JLC04161H-7628 stackup, 1.0 oz copper, ENIG finish, 0 DRC violations).
- **Battery Architecture:** Removable below-rail conformal cradle with positive mechanical clearances.
  - **Selected Commercial Cell:** Model `LP300830-PCM` ($50\text{ mAh}$ nominal, $3.7\text{ V}$ LiPo).
  - **Maximum Finished Pack Envelope:** $33.00\text{ mm}$ (L) $\times 8.20\text{ mm}$ (W) $\times 3.30\text{ mm}$ (T) with integrated PCM and silicone leads.
  - **Cradle Cavity:** $34.00\text{ mm}$ (L) $\times 8.40\text{ mm}$ (W) $\times 3.50\text{ mm}$ (T) ($+0.20\text{ mm}$ thickness, $+0.20\text{ mm}$ width, $+1.00\text{ mm}$ length clearance).
  - **Bore Clearance:** $+0.437\text{ mm}$ corner clearance to barrel inner bore; $+0.25\text{ mm}$ clearance to moving pushrod tunnel.
- **Charging & Thermal Safety:**
  - $R_9 = 20.0\text{ k}\Omega \implies 50.0\text{ mA}$ charge current ($1.0\text{C}$ rating).
  - MCP73831 worst-case thermal dissipation: $P_D = (5.0\text{ V} - 3.0\text{ V}) \times 50.0\text{ mA} = \mathbf{100.0\text{ mW}}$, $\Delta T_{\text{IC}} = 23.0^\circ\text{C}$, $T_{J,\text{IC}} = 48.0^\circ\text{C}$ (well below $125.0^\circ\text{C}$ silicon junction limit).
  - Battery pouch cell surface temperature: $T_{\text{cell}} \le 30.0^\circ\text{C}$ (well below $+45.0^\circ\text{C}$ IEC 62133-2 charging limit).
- **Power-Path & Diode Circuitry:**
  - **`D4`** is the USB power-path OR-ing diode (`1N5819HW-7-F` / `MBR0520L`, SOD-123) connecting `USB_VBUS` to `VSYS_RAW`.
  - **`D3`** is the haptic motor flyback clamp diode (`1N5819HW-7-F`, SOD-123) across motor `M1`.
  - Power path P-FET $Q_2$ (`DMG2305UX`) turns firmly OFF when USB is attached ($V_{GS} = +0.35\text{ V}$), body diode reverse-biased by $-0.45\text{ V}$, completely isolating the battery.
- **Native Mechanical CAD Validation:**
  - 29/29 STEP files validated with valid BRep topology and non-zero volume by FreeCAD 0.19 on GitHub Actions Ubuntu 22.04 ([Run 44128253975](https://github.com/SIDDARTHA577/smart-pen-pcb-design/actions/runs/44128253975)).
  - Local Windows development workstation execution is restricted by host WDAC policy.
  - Complete 27-body assembly confirmed $0.0000\text{ mm}^3$ collision across all 351 pairwise intersections.

---

## 3. Explicit Engineering Limitations & Prototype Requirements

This deliverable is strictly a **Digital Design Package**. Physical testing has not been performed and must be executed during client prototype bring-up:
1. **Battery Sourcing & Certification:** Exact battery supplier and protected-pack specification (`LP300830-PCM`) are uncertified by physical hardware testing. UN 38.3 transport, IEC 62133-2 safety, and actual runtime require physical vendor test reports and first-article prototype testing.
2. **Wi-Fi High-Power Operation:** Full-power Wi-Fi transmission ($385\text{ mA}$ peak) is designed and thermally allocated for USB-connected operation only. Firmware enforcement is an external software integration requirement and has not been implemented or verified in this digital hardware release.
3. **RF OTA Performance:** Antenna return loss ($S_{11}$), radiation efficiency, and human hand detuning require physical RF anechoic chamber testing.
4. **Physical Assembly & Wear:** Click mechanism kinematics ($4.50\text{ mm}$ travel) and tolerances ($0.0000\text{ mm}^3$ CAD clash) require physical 3D print or injection molded prototype assembly and cyclic endurance testing.

---

## 4. Package Checksums & Integrity

All files in this archive have been cryptographically hashed (SHA-256) directly from the uncompressed byte streams inside the archive. Refer to `SHA256_FINAL_DELIVERY_MANIFEST.txt` for the authoritative checksums.

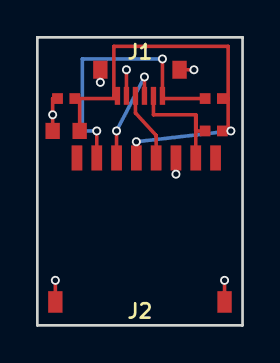
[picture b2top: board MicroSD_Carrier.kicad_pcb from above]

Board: 2 copper layers, 11.4 x 16.0 mm, 6 parts (0 on the bottom side), 6 nets.

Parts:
C1: 0.1uF; C_0402
C2: 10uF; C_0603
J1: FH12-6S-0.5SH; FPC_6P_0.5mm
J2: TF-01A; MicroSD_Socket_TF01A
R1, R2: 10k; R_0402

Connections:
/3V3: C1.1, C2.1, J1.1, J2.4, R1.1, R2.1
/GND: C1.2, C2.2, J1.2, J1.MP1, J1.MP2, J2.6, J2.9, J2.10
/SD_CS: J1.6, J2.2, R1.2
/SD_MISO: J1.5, J2.7, R2.2
/SD_MOSI: J1.4, J2.3
/SD_SCK: J1.3, J2.5

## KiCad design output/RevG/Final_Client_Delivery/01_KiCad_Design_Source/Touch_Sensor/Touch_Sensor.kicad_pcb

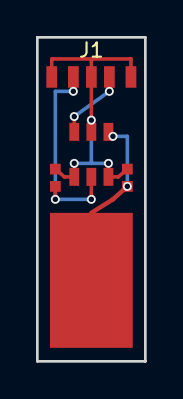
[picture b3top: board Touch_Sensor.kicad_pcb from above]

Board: 2 copper layers, 6.0 x 18.0 mm, 5 parts (0 on the bottom side), 4 nets.

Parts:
C1: 0.1uF; C_0402
C2: 10pF; C_0402
E1: TOUCH_PAD; Touch_Pad_5x10mm
J1: SM03B-SRSS-TB; JST_SH_3P
U1: TTP223-BA6; SOT-23-6

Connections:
/3V3: C1.1, J1.1, U1.5
/GND: C1.2, C2.2, J1.2, J1.4, U1.2, U1.4, U1.6
/TOUCH_IN: C2.1, E1.1, U1.3
/TOUCH_OUT: J1.3, U1.1

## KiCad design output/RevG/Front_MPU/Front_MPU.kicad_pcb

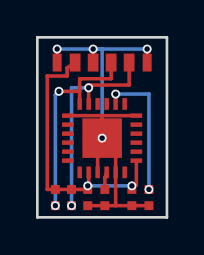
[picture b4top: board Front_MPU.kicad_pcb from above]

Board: 2 copper layers, 7.2 x 10.0 mm, 8 parts (0 on the bottom side), 6 nets.

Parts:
C1, C2, C4: 0.1uF; C_0402
C3: 2.2nF; C_0402
J1: SM04B-SRSS-TB; JST_SH_4P
R1, R2: 4.7k; R_0402
U1: MPU-6050; QFN-24_4x4mm

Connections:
/3V3: C1.1, C2.1, J1.1, R1.1, R2.1, U1.8, U1.13
/CPOUT: C3.1, U1.20
/GND: C1.2, C2.2, C3.2, C4.2, J1.2, J1.5, U1.1, U1.9, U1.11, U1.18, U1.25
/I2C_SCL: J1.4, R1.2, U1.23
/I2C_SDA: J1.3, R2.2, U1.24
/REGOUT: C4.1, U1.10

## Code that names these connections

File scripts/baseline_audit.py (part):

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1. **MCP73831 is NOT a Power-Path Regulator**:
   - The schematic uses U2 (`MCP73831T-2ACI/OT`) as a basic linear LiPo charger.
   - MCP73831 has NO power-path management (no automatic switchover between VBUS and VBAT). If the pen operates while charging, system current robs charge current from the termination sensing loop, potentially preventing charge termination or overheating the battery.
   - `CHG_STAT` (U2 pin 1) is floating (single-pin net, no MCU monitoring or LED indication).
2. **Missing 3.3 V Regulator (`J_PWR`)**:
   - The 3.3V supply is represented as a dummy header `J_PWR` (`REGULATOR_CARD_TBD`) rather than an onboard low-noise, high-PSR buck/buck-boost or high-current LDO.
   - ESP32-C3 requires >=500 mA peak transient capability for RF transmission bursts.
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
### 3.2 ESP32-C3 Core & Strapping Verification
1. **Strapping Pins Allocation**:
   - `GPIO9` (BOOT / Strapping): Pulled high via R2 (10k) with SW2 to GND. (PASS)
   - `GPIO2` (Strapping): Pulled high via R3 (10k). (PASS)
   - `GPIO8` (Strapping): High during download boot. Currently floating in Rev D schematic.
2. **VDD_SPI & Internal Flash**:
   - U1 is `ESP32-C3FH4X` with 4MB embedded flash. Pin 18 (`VDD_SPI`) is decoupled by C5 (1uF). It is internally driven by an on-chip LDO and must NOT be connected to external 3.3V power. Rev D correctly keeps it isolated to C5.
3. **Clock / Crystal Circuit**:
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
### 3.4 Peripheral & Sensor Deficiencies
1. **Front IMU (`J_IMU`)**:
   - Connected via `CONN_4P_TBD` to I2C bus (`I2C_SDA` on GPIO0, `I2C_SCL` on GPIO1).
   - Needs rigid mechanical retention, strain relief, and standardized keyed 1.0mm/1.25mm connector (e.g., JST SH or Molex PicoBlade).
2. **MicroSD Carrier (`J_SD`)**:
   - Connected via 6-pin remote header `CONN_6P_TBD` rather than an integrated micro-profile push-pull MicroSD socket, due to previous 9.4 mm board width constraints.
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
## 5. Summary of Baseline Tests
- **KiCad ERC/DRC**: BLOCKED (EasyEDA format, KiCad CLI not natively installed).
- **Static Netlist Consistency**: 42 nets, 180 connections. 1 single-pin net (`CHG_STAT`).
- **PCB Parity**: 20 schematic components missing from PCB layout.
- **Manufacturing Readiness**: **FAIL** (Draft/Review stage only).
"""
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
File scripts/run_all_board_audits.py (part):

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
### 2.2 Front MPU Daughterboard (`Front_MPU`)
- **Function:** Writing tip motion and gesture tracking module mounted directly in the pen tip carrier.
- **Hardware Architecture:** InvenSense MPU-6050 (QFN-24 4x4mm), C1 (0.1µF VDD), C2 (0.1µF VLOGIC), C3 (2.2nF CPOUT charge pump), C4 (0.1µF REGOUT LDO filter), R1 (4.7k SCL pull-up), R2 (4.7k SDA pull-up), J1 (JST SH 4-pin 1.0mm pitch SMD connector).
- **Pinout & Address:** AD0 pulled to GND (I2C address `0x68`), CLKIN to GND, FSYNC to GND. Pinout matches Main PCB `J_IMU`: `1: 3V3, 2: GND, 3: I2C_SDA, 4: I2C_SCL`.
- **ERC CLI Execution:**
  ```powershell
  {results[3]['erc_cmd']}
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
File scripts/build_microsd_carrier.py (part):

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        '  (label "GND" (at 45.72 86.36 180) (effects (font (size 1.27 1.27)) (justify right)))',
        # J1 Pin 3 (SCK) at (53.34 88.90)
        '  (wire (pts (xy 53.34 88.90) (xy 45.72 88.90)) (stroke (width 0)))',
        '  (label "SD_SCK" (at 45.72 88.90 180) (effects (font (size 1.27 1.27)) (justify right)))',
        # J1 Pin 4 (MOSI) at (53.34 91.44)
        '  (wire (pts (xy 53.34 91.44) (xy 45.72 91.44)) (stroke (width 0)))',
        '  (label "SD_MOSI" (at 45.72 91.44 180) (effects (font (size 1.27 1.27)) (justify right)))',
        # J1 Pin 5 (MISO) at (53.34 93.98)
        '  (wire (pts (xy 53.34 93.98) (xy 45.72 93.98)) (stroke (width 0)))',
        '  (label "SD_MISO" (at 45.72 93.98 180) (effects (font (size 1.27 1.27)) (justify right)))',
        # J1 Pin 6 (CS) at (53.34 96.52)
        '  (wire (pts (xy 53.34 96.52) (xy 45.72 96.52)) (stroke (width 0)))',
        '  (label "SD_CS" (at 45.72 96.52 180) (effects (font (size 1.27 1.27)) (justify right)))',

        # J2 Socket Pins
        # Pin 2 (CS) at (137.16 81.28)
        '  (wire (pts (xy 137.16 81.28) (xy 144.78 81.28)) (stroke (width 0)))',
        '  (label "SD_CS" (at 144.78 81.28 0) (effects (font (size 1.27 1.27)) (justify left)))',
        # Pin 3 (MOSI) at (137.16 83.82)
        '  (wire (pts (xy 137.16 83.82) (xy 144.78 83.82)) (stroke (width 0)))',
        '  (label "SD_MOSI" (at 144.78 83.82 0) (effects (font (size 1.27 1.27)) (justify left)))',
        # Pin 4 (VDD) at (137.16 86.36)
        '  (wire (pts (xy 137.16 86.36) (xy 144.78 86.36)) (stroke (width 0)))',
        '  (label "3V3" (at 144.78 86.36 0) (effects (font (size 1.27 1.27)) (justify left)))',
        # Pin 5 (SCK) at (137.16 88.90)
        '  (wire (pts (xy 137.16 88.90) (xy 144.78 88.90)) (stroke (width 0)))',
        '  (label "SD_SCK" (at 144.78 88.90 0) (effects (font (size 1.27 1.27)) (justify left)))',
        # Pin 6 (VSS) at (137.16 91.44)
        '  (wire (pts (xy 137.16 91.44) (xy 144.78 91.44)) (stroke (width 0)))',
        '  (label "GND" (at 144.78 91.44 0) (effects (font (size 1.27 1.27)) (justify left)))',
        # Pin 7 (MISO) at (137.16 93.98)
        '  (wire (pts (xy 137.16 93.98) (xy 144.78 93.98)) (stroke (width 0)))',
        '  (label "SD_MISO" (at 144.78 93.98 0) (effects (font (size 1.27 1.27)) (justify left)))',
        # Pin 9, 10 (Shields) to GND
        '  (wire (pts (xy 137.16 99.06) (xy 144.78 99.06)) (stroke (width 0)))',
        '  (label "GND" (at 144.78 99.06 0) (effects (font (size 1.27 1.27)) (justify left)))',
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        '  (wire (pts (xy 88.90 93.98) (xy 88.90 88.90)) (stroke (width 0)))',
        '  (label "3V3" (at 88.90 88.90 90) (effects (font (size 1.27 1.27)) (justify left)))',
        '  (wire (pts (xy 88.90 99.06) (xy 88.90 104.14)) (stroke (width 0)))',
        '  (label "SD_CS" (at 88.90 104.14 270) (effects (font (size 1.27 1.27)) (justify right)))',
        '  (wire (pts (xy 99.06 93.98) (xy 99.06 88.90)) (stroke (width 0)))',
        '  (label "3V3" (at 99.06 88.90 90) (effects (font (size 1.27 1.27)) (justify left)))',
        '  (wire (pts (xy 99.06 99.06) (xy 99.06 104.14)) (stroke (width 0)))',
        '  (label "SD_MISO" (at 99.06 104.14 270) (effects (font (size 1.27 1.27)) (justify right)))'
    ]
    sch_lines.extend(wires)
    sch_lines.append(')')
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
